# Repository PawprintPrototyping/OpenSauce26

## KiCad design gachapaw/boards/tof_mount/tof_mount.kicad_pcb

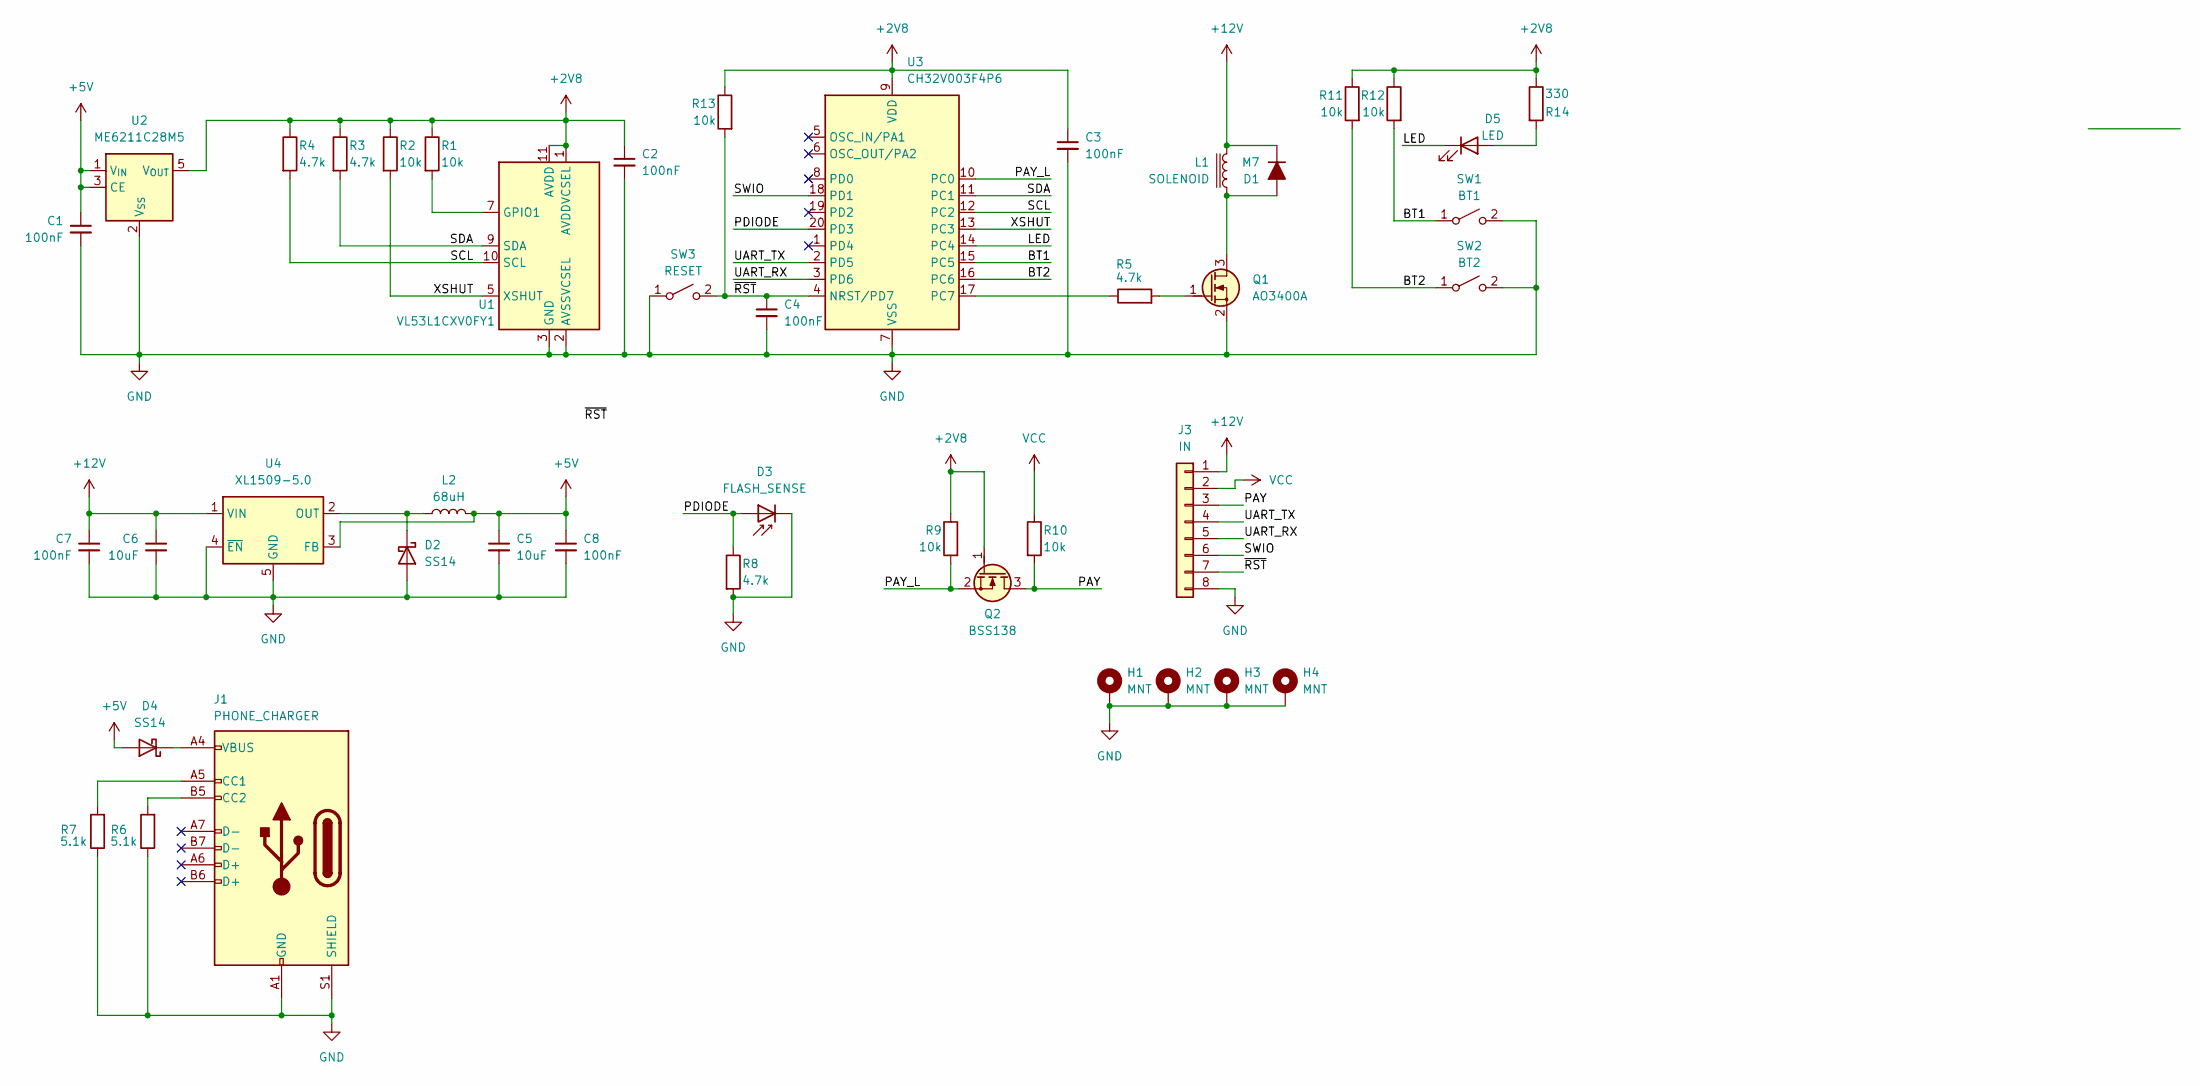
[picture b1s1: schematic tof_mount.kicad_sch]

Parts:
C1, C2, C3, C4, C7, C8: 100nF; C_0402_1005Metric
C5, C6: 10uF; C_0805_2012Metric
D1: M7; D_SMA
D2, D4: SS14; D_SMA
D3: FLASH_SENSE; PinHeader_1x02_P2.54mm_Vertical
D5: LED; R_0603_1608Metric
H1, H2, H3, H4: MNT; MountingHole_2.2mm_M2_Pad_Via
J1: PHONE_CHARGER; USB_C_Receptacle_G-Switch_GT-USB-7010ASV
J3: IN; PinHeader_1x08_P2.54mm_Vertical
L1: SOLENOID; PinHeader_1x02_P2.54mm_Vertical
L2: 68uH; L_SXN_SMDRI127
Q1: AO3400A; SOT-23
Q2: BSS138; SOT-23
R1, R2, R9, R10, R11, R12, R13: 10k; R_0402_1005Metric
R3, R4, R5, R8: 4.7k; R_0402_1005Metric
R6, R7: 5.1k; R_0402_1005Metric
R14: 330; R_0402_1005Metric
SW1: BT1; SW_SPST_EVPBF
SW2: BT2; SW_SPST_EVPBF
SW3: RESET; SW_SPST_EVPBF
U1: VL53L1CXV0FY1; ST_VL53L1x
U2: ME6211C28M5; SOT-23-5
U3: CH32V003F4P6; TSSOP-20_4.4x6.5mm_P0.65mm
U4: XL1509-5.0; SOIC-8_3.9x4.9mm_P1.27mm

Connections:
+2V8: C2.1, C3.1, Q2.1 (G), R1.1, R2.1, R3.1, R4.1, R9.1, R11.1, R12.1, R13.1, R14.1, U1.1 (AVDDVCSEL), U1.11 (AVDD), U2.5 (V_{OUT}), U3.9 (VDD)
+5V: C1.1, C5.1, C8.1, D4.2 (A), L2.2, U2.1 (V_{IN}), U2.3 (CE), U4.3 (FB)
+12V: C6.1, C7.1, D1.1 (K), J3.1, L1.1, U4.1 (VIN)
/BT1: R12.2, SW1.1 (A), U3.15 (PC5)
/BT2: R11.2, SW2.1 (A), U3.16 (PC6)
/LED: D5.1 (K), U3.14 (PC4)
/PAY: J3.3, Q2.3 (D), R10.2
/PAY_L: Q2.2 (S), R9.2, U3.10 (PC0)
/PDIODE: D3.2 (A), R8.1, U3.20 (PD3)
/SCL: R4.2, U1.10 (SCL), U3.12 (PC2)
/SDA: R3.2, U1.9 (SDA), U3.11 (PC1)
/SWIO: J3.6, U3.18 (PD1)
/UART_RX: J3.5, U3.3 (PD6)
/UART_TX: J3.4, U3.2 (PD5)
/XSHUT: R2.2, U1.5 (XSHUT), U3.13 (PC3)
/~RST: C4.1, J3.7, R13.2, SW3.2 (B), U3.4 (NRST/PD7)
GND: C1.2, C2.2, C3.2, C4.2, C5.2, C6.2, C7.2, C8.2, D2.2 (A), D3.1 (K), H1.1, H2.1, H3.1, H4.1, J1.A1 (GND), J1.A12 (GND), J1.B1 (GND), J1.B12 (GND), J1.S1 (SHIELD), J3.8, Q1.2 (S), R6.1, R7.1, R8.2, SW1.2 (B), SW2.2 (B), SW3.1 (A), U1.2 (AVSSVCSEL), U1.3 (GND), U1.4 (GND), U1.6 (GND), U1.12 (GND), U2.2 (V_{SS}), U3.7 (VSS), U4.4 (~EN), U4.5 (GND), U4.6 (GND), U4.7 (GND), U4.8 (GND)
unnamed: D1.2 (A), L1.2, Q1.3 (D)
unnamed: D2.1 (K), L2.1, U4.2 (OUT)
unnamed: D4.1 (K), J1.A4 (VBUS), J1.A9 (VBUS), J1.B4 (VBUS), J1.B9 (VBUS)
unnamed: D5.2 (A), R14.2
unnamed: J1.A5 (CC1), R7.2
unnamed: J1.B5 (CC2), R6.2
unnamed: Q1.1 (G), R5.2
unnamed: R1.2, U1.7 (GPIO1)
unnamed: R5.1, U3.17 (PC7)
VCC: J3.2, R10.1

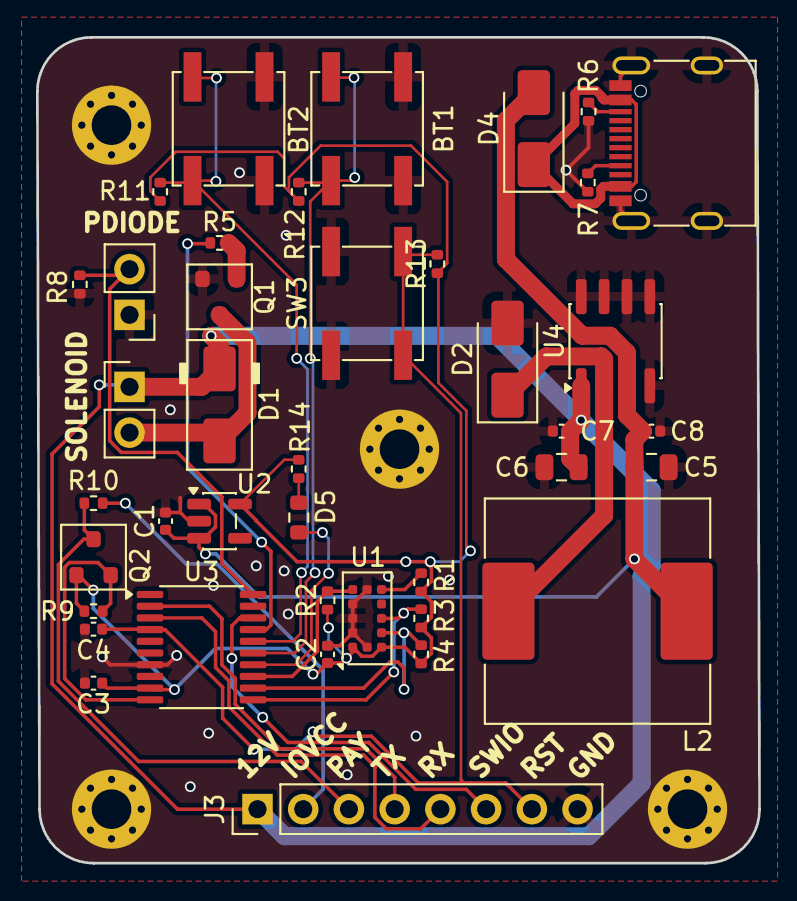
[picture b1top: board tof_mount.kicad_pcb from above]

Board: 2 copper layers, 40.1 x 45.9 mm, 44 parts (0 on the bottom side), 27 nets.

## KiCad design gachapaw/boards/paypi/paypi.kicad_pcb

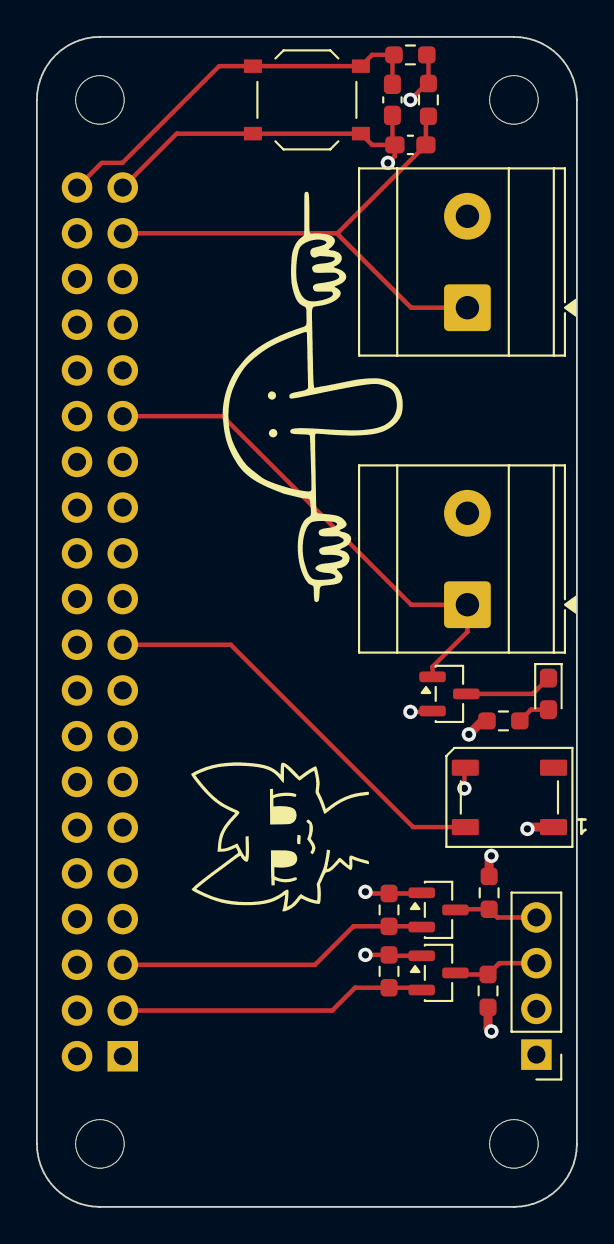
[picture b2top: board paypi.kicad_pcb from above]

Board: 4 copper layers, 30.0 x 65.0 mm, 19 parts (1 on the bottom side), 13 nets.

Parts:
C1, C2: 100n; C_0603_1608Metric_Pad1.08x0.95mm_HandSolder
D1: RED; LED_0603_1608Metric_Pad1.05x0.95mm_HandSolder
D2: WS2812B; LED_WS2812B_PLCC4_5.0x5.0mm_P3.2mm
J1: Conn_02x20_Odd_Even; PinSocket_2x20_P2.54mm_Vertical
J2: Conn_01x02; TerminalBlock_Phoenix_MKDS-3-2-5.08_1x02_P5.08mm_Horizontal
J3: Conn_01x04; PinHeader_1x04_P2.54mm_Vertical
Q1, Q2, Q3: AO3400A; SOT-23
R1, R2: 10k; R_0603_1608Metric_Pad0.98x0.95mm_HandSolder
R3, R5, R6, R7: 4k7; R_0603_1608Metric_Pad0.98x0.95mm_HandSolder
R4: 330; R_0603_1608Metric_Pad0.98x0.95mm_HandSolder
SW1: SW_Push; SW_Push_1P1T_XKB_TS-1187A
SW2: SW_Push; TerminalBlock_Phoenix_MKDS-3-2-5.08_1x02_P5.08mm_Horizontal

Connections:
+3V3: J1.1, J1.17, Q2.1 (G), Q3.1 (G), R1.1, R2.1, R3.1, R6.1
+5V: D2.1 (VDD), J1.2, J1.4, J3.2, R4.1, R5.1, R7.1
/SCL: J3.4, Q3.3 (D), R7.2
/SDA: J3.3, Q2.3 (D), R5.2
BTN: C1.1, J1.37, R1.2, SW2.1
GND: C1.2, C2.2, D2.3 (VSS), J1.6, J1.9, J1.14, J1.20, J1.25, J1.30, J1.34, J1.39, J2.2, J3.1, Q1.2 (S), SW1.2, SW2.2
GPIO: J1.29, J2.1, Q1.1 (G)
unnamed: D1.2 (A), R4.2
unnamed: D1.1 (K), Q1.3 (D)
PI_SCL: J1.5, Q3.2 (S), R6.2
PI_SDA: J1.3, Q2.2 (S), R3.2
PWR: C2.1, J1.40, R2.2, SW1.1
STATUS: D2.4 (DIN), J1.19

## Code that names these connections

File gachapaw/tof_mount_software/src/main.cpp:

#include <Arduino.h>
#include <Wire.h>
#include <VL53L1X.h>

// --- Debug Macro Configuration ---
#ifdef DEBUG_ENABLE
  #define DEBUG_BEGIN(baud)    Serial.begin(baud)
  #define DEBUG_PRINT(x)       Serial.print(x)
  #define DEBUG_PRINTLN(x)     Serial.println(x)
#else
  #define DEBUG_BEGIN(baud)
  #define DEBUG_PRINT(x)
  #define DEBUG_PRINTLN(x)
#endif

// Hardware Pin Configuration
constexpr uint8_t PIN_PAY_L      = PC0; // Input from RPi - successful payment when driven LOW
constexpr uint8_t PIN_SDA        = PC1; 
constexpr uint8_t PIN_SCL        = PC2; 
constexpr uint8_t PIN_XSHUT      = PC3; 
constexpr uint8_t PIN_LED_L      = PC4; // Active Low LED
constexpr uint8_t PIN_TRIGGER    = PC5; // BT1 - Simulates PIN_PAY trigger
constexpr uint8_t PIN_MANUAL     = PC6; // BT2 - Manual Override Button for solenoid
constexpr uint8_t PIN_SOLENOID   = PC7; // solenoid output

// System Constants
constexpr uint16_t I2C_SPEED_KHZ           = 400000;
constexpr uint16_t DETECTION_THRESHOLD_MM  = 30; 
constexpr uint32_t DEBOUNCE_DELAY_MS       = 30;
constexpr uint32_t POST_DETECTION_DELAY_MS = 3000;
constexpr uint8_t  CALIBRATION_SAMPLES     = 10;
constexpr uint16_t TOF_TIMING_BUDGET_US    = 20000; 

VL53L1X sensor;

enum class SystemState {
    INIT,
    CALIBRATING,
    WAIT_FOR_TRIGGER,
    WAIT_FOR_BALL,
    POST_DETECTION_DELAY,
    ERROR
};

SystemState currentState = SystemState::INIT;
uint16_t baselineDistanceMm = 0;

uint32_t lastTriggerTime = 0;
uint32_t lastManualDebounceTime = 0;
uint32_t ballDetectedTime = 0;
bool lastManualBtnState = HIGH;
bool manualBtnHandled = false;

void setup() {
    DEBUG_BEGIN(115200);
    DEBUG_PRINTLN("SYS: Booting...");

    pinMode(PIN_PAY_L, INPUT_PULLUP);
    pinMode(PIN_TRIGGER, INPUT_PULLUP);
    pinMode(PIN_MANUAL, INPUT_PULLUP);
    
    pinMode(PIN_SOLENOID, OUTPUT);
    digitalWrite(PIN_SOLENOID, LOW); 
    
    pinMode(PIN_LED_L, OUTPUT);
    digitalWrite(PIN_LED_L, HIGH); // LED OFF

    // 1. Hardware Reset the VL53L1X
    DEBUG_PRINTLN("SYS: Resetting ToF...");
    pinMode(PIN_XSHUT, OUTPUT);
    digitalWrite(PIN_XSHUT, LOW);  
    delay(10);
    digitalWrite(PIN_XSHUT, HIGH); 
    delay(10);                     

    // 2. Initialize I2C 
    Wire.begin();
    Wire.setClock(I2C_SPEED_KHZ);

    // 3. Initialize Sensor
    sensor.setTimeout(500);
    if (!sensor.init()) {
        DEBUG_PRINTLN("ERR: ToF Init Failed!");
        currentState = SystemState::ERROR;
        return;
    }

    sensor.setDistanceMode(VL53L1X::Short);
    sensor.setMeasurementTimingBudget(TOF_TIMING_BUDGET_US);
    sensor.startContinuous(TOF_TIMING_BUDGET_US / 1000); 

    DEBUG_PRINTLN("SYS: Calibration started.");
    currentState = SystemState::CALIBRATING;
}

void loop() {
    // --- Global Manual Override Evaluation ---
    bool currentBtnState = digitalRead(PIN_MANUAL);
    if (currentBtnState != lastManualBtnState) {
        lastManualDebounceTime = millis();
    }

    if ((millis() - lastManualDebounceTime) > DEBOUNCE_DELAY_MS) {
        if (currentBtnState == LOW && !manualBtnHandled) {
            bool isSolenoidOn = digitalRead(PIN_SOLENOID);
            digitalWrite(PIN_SOLENOID, !isSolenoidOn);
            
            DEBUG_PRINT("EVT: Solenoid Manual ");
            DEBUG_PRINTLN(!isSolenoidOn ? "ON" : "OFF");
            
            manualBtnHandled = true;
        } else if (currentBtnState == HIGH) {
            manualBtnHandled = false;
        }
    }
    lastManualBtnState = currentBtnState;

    // --- Core State Machine ---
    switch (currentState) {
        case SystemState::INIT:
            break;

        case SystemState::CALIBRATING: {
            uint32_t sum = 0;
            uint8_t validSamples = 0;

            for (uint8_t i = 0; i < CALIBRATION_SAMPLES; i++) {
                sensor.read();
                if (!sensor.timeoutOccurred()) {
                    sum += sensor.ranging_data.range_mm;
                    validSamples++;
                }
            }

            if (validSamples > (CALIBRATION_SAMPLES / 2)) {
                baselineDistanceMm = sum / validSamples;
                
                DEBUG_PRINT("SYS: Calibration OK. Baseline: ");
                DEBUG_PRINT(baselineDistanceMm);
                DEBUG_PRINTLN(" mm");
                
                currentState = SystemState::WAIT_FOR_TRIGGER;
            } else {
                DEBUG_PRINTLN("ERR: Calibration failed.");
                currentState = SystemState::ERROR;
            }
            break;
        }

        case SystemState::WAIT_FOR_TRIGGER: {
            if (digitalRead(PIN_TRIGGER) == LOW || digitalRead(PIN_PAY_L) == LOW) {
                if (lastTriggerTime == 0) { 
                    lastTriggerTime = millis();
                } else if ((millis() - lastTriggerTime) > DEBOUNCE_DELAY_MS) {
                    digitalWrite(PIN_LED_L, LOW); // LED ON
                    digitalWrite(PIN_SOLENOID, HIGH); 
                    lastTriggerTime = 0;
                    
                    DEBUG_PRINTLN("EVT: Trigger Armed.");
                    currentState = SystemState::WAIT_FOR_BALL;
                }
            } else {
                lastTriggerTime = 0;
            }
            break;
        }

        case SystemState::WAIT_FOR_BALL: {
            sensor.read();
            if (!sensor.timeoutOccurred()) {
                uint16_t currentDistance = sensor.ranging_data.range_mm;
                
                if (currentDistance < (baselineDistanceMm - DETECTION_THRESHOLD_MM)) {
                    DEBUG_PRINT("EVT: Ball Detected! Dist: ");
                    DEBUG_PRINT(currentDistance);
                    DEBUG_PRINTLN(" mm. Starting delay.");
                    
                    ballDetectedTime = millis(); // Record detection time
                    currentState = SystemState::POST_DETECTION_DELAY;
                }
            }
            break;
        }

        case SystemState::POST_DETECTION_DELAY: {
            // Wait for the configured delay before turning off the solenoid
            if ((millis() - ballDetectedTime) >= POST_DETECTION_DELAY_MS) {
                digitalWrite(PIN_LED_L, HIGH); // LED OFF
                digitalWrite(PIN_SOLENOID, LOW); 
                
                DEBUG_PRINTLN("EVT: Post-detection delay complete.");
                currentState = SystemState::WAIT_FOR_TRIGGER;
            }
            break;
        }

        case SystemState::ERROR:
            digitalWrite(PIN_LED_L, !digitalRead(PIN_LED_L));
            delay(250); 
            break;
    }
}

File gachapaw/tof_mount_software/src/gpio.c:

#include "ch32fun.h"
#include "gpio.h"

// PD3 = ADC channel 4
#define PHOTODIODE_ADC_CH 4

void gpio_init(void) {
    funGpioInitAll();

    // PC7: relay output (push-pull)
    funPinMode(PC7, GPIO_CFGLR_OUT_10Mhz_PP);
    GPIOC->BCR = (1 << 7);

    // PC4: LED output (push-pull)
    funPinMode(PC4, GPIO_CFGLR_OUT_10Mhz_PP);
    GPIOC->BCR = (1 << 4);

    // PC5: button 1, input with pull-up
    funPinMode(PC5, GPIO_CFGLR_IN_PUPD);
    GPIOC->BSHR = (1 << 5);

    // PC6: button 2, input with pull-up
    funPinMode(PC6, GPIO_CFGLR_IN_PUPD);
    GPIOC->BSHR = (1 << 6);

    // PC0: pay pin, floating input (external pull-up via BSS138 level translator)
    funPinMode(PC0, GPIO_CFGLR_IN_FLOAT);

    // PD3: photodiode, analog input
    funPinMode(PD3, GPIO_CFGLR_IN_ANALOG);

    // ADC setup
    RCC->APB2PCENR |= RCC_APB2Periph_ADC1;
    RCC->CFGR0 = (RCC->CFGR0 & ~RCC_ADCPRE) | RCC_ADCPRE_DIV6;

    ADC1->CTLR2 |= ADC_ADON;
    Delay_Ms(1);

    // Calibrate
    ADC1->CTLR2 |= ADC_RSTCAL;
    while (ADC1->CTLR2 & ADC_RSTCAL);
    ADC1->CTLR2 |= ADC_CAL;
    while (ADC1->CTLR2 & ADC_CAL);

    // 241 cycle sample time for channel 4
    ADC1->SAMPTR2 = (ADC1->SAMPTR2 & ~(7 << (3 * PHOTODIODE_ADC_CH)))
                    | (7 << (3 * PHOTODIODE_ADC_CH));
}

void relay_on(void)          { GPIOC->BSHR = (1 << 7); }
void relay_off(void)         { GPIOC->BCR  = (1 << 7); }
void relay_set(uint8_t on)   { if (on) relay_on(); else relay_off(); }

void led_on(void)            { GPIOC->BSHR = (1 << 4); }
void led_off(void)           { GPIOC->BCR  = (1 << 4); }
void led_set(uint8_t on)     { if (on) led_on(); else led_off(); }
void led_toggle(void)        { GPIOC->OUTDR ^= (1 << 4); }

uint8_t button1_read(void)   { return !(GPIOC->INDR & (1 << 5)); }
uint8_t button2_read(void)   { return !(GPIOC->INDR & (1 << 6)); }

uint8_t pay_read(void)       { return !(GPIOC->INDR & (1 << 0)); }

uint16_t photodiode_read(void) {
    ADC1->RSQR3 = PHOTODIODE_ADC_CH;
    ADC1->CTLR2 |= ADC_SWSTART | ADC_EXTTRIG | ADC_EXTSEL;
    while (!(ADC1->STATR & ADC_EOC));
    ADC1->STATR &= ~ADC_EOC;
    return ADC1->RDATAR;
}

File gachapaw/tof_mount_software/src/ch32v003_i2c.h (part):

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 *  ------ WORK IN PROGRESS !!! -------
 * 
 * I2C pin mapping:
 * SCL=PC2, SDA=PC1, AFIO_PCFR1.I2C1REMAP1= 0, I2C1RM = 0 
 * SCL=PD1, SDA=PD0, AFIO_PCFR1.I2C1REMAP1= 0, I2C1RM = 1   <-- PD1 = SWIO !!!
 * SCL=PC5, SDA=PC6, AFIO_PCFR1.I2C1REMAP1= 1, I2C1RM = X
 * 
 * Usage:
 * 
 * 1. Optionally choose one of the altenate configurations, if not, 
 * 		the default setting (PC2+PC1) will be used 
 * #define I2C_PINS_SCLPD1_SDAPD0
 * #define I2C_PINS_SCLPC5_SDAPC6
 *
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
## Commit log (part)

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2026-02-19 Kickoff Notes
2026-02-26 Agenda 2_26 Update
2026-02-26 Finish 2_26 update
2026-03-05 Notes 3/4
2026-03-05 Clarify mech tasks
2026-03-12 Notes for 3_11
2026-03-19 Notes for 3_18
2026-03-27 first pass design of tof (Time of Flight) board for the gachapaw
2026-04-09 Create 4_8_26.md
    notes for 4/8
2026-04-16 very basic software
2026-04-16 Create 4_15_26
2026-04-16 extremely basic init function
2026-04-30 4_28 notes
2026-05-07 5_26_notes
2026-05-21 Meeting Notes for 5/20/26
2026-05-25 WIP Gashapaw app PoC phase 1
    PoC complete for: neopixel and gpio output.
    Next:
    - 1604 LCD screen
    - input gpio pin
2026-05-25 fix up commit
2026-05-25 paypi hw
2026-05-28 Notes for 5/27 meeting
2026-05-28 WIP Gashapaw app PoC phase 2
    - Add liquidcrystal submodule
    PoC complete for: neopixel and gpio output, 604 LCD screen, and input gpio pin
2026-06-08 WIP Gashapaw app PoC phase 3
    - Add square PoS SDK support
    PoC complete for: liquidcrystal, neopixel and gpio output, 604 LCD screen, and input gpio pin
2026-06-11 Notes for 6/10 Meeting
2026-06-14 Update notes
2026-06-18 Meeting note 6/17
2026-06-28 Gashapaw refactor to prepare for state machine

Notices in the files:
gachapaw/tof_mount_software/src/ch32v003_i2c.h:
Copyright (c) 2023 Piotr Zapart
